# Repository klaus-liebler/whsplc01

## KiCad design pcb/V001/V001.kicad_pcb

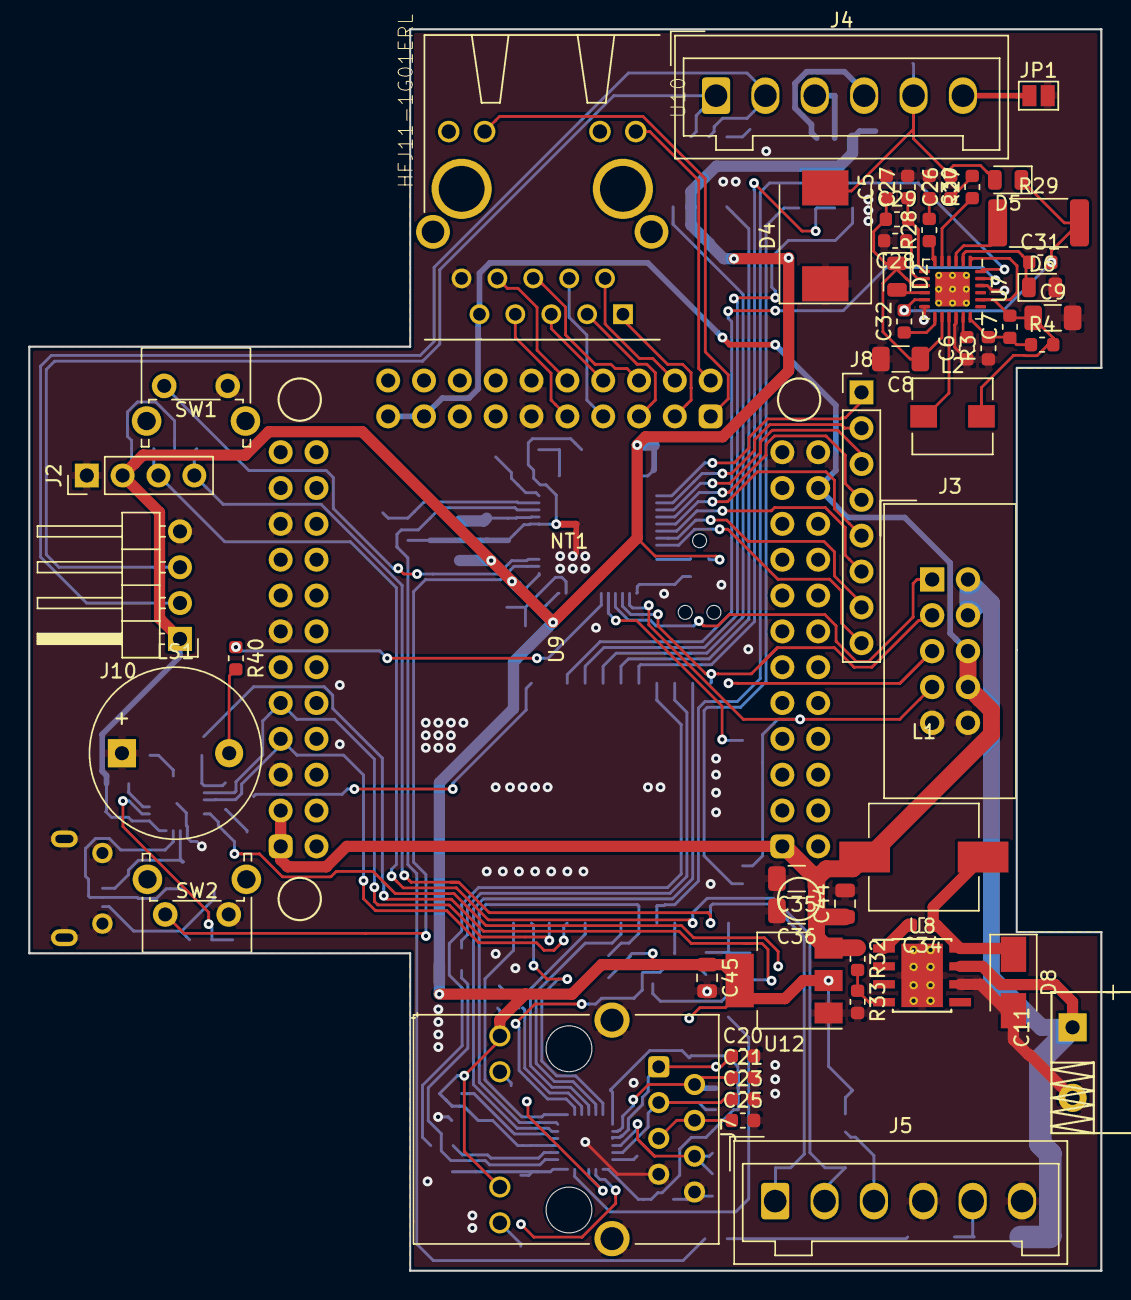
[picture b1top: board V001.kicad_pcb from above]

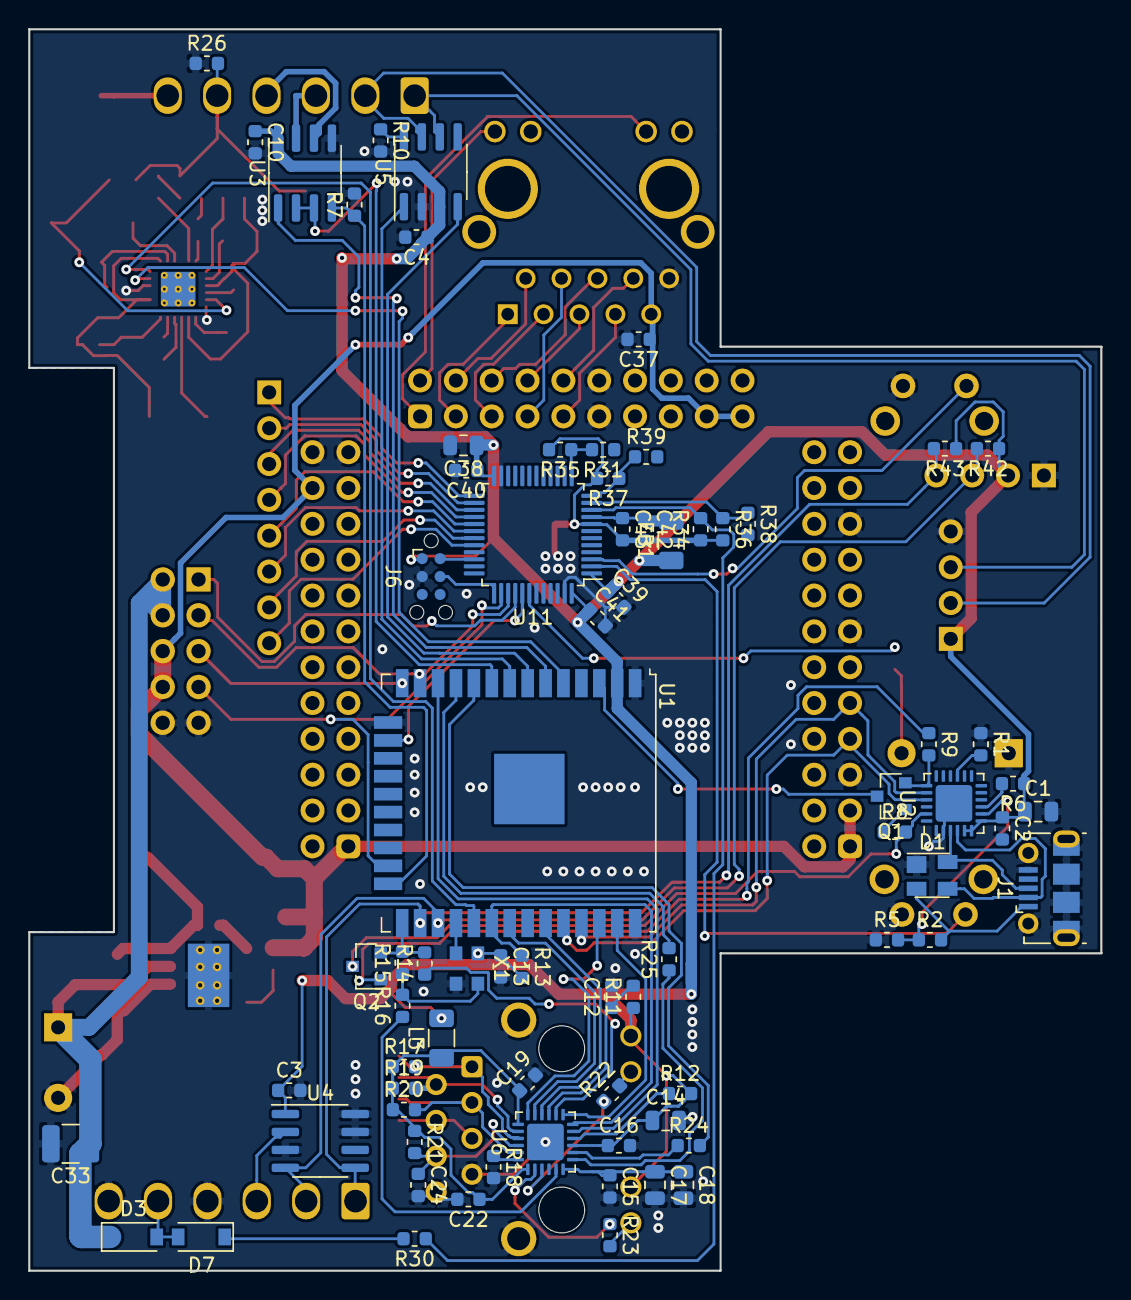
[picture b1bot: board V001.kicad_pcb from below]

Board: 2 copper layers, 76.0 x 88.0 mm, 128 parts (74 on the bottom side), 119 nets.

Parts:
C1: 4u7/6V3; C_0805_2012Metric
C2: u1/6V3; C_0603_1608Metric
C3, C4, C10, C12, C13, C16, C19, C22, C39, C40, C41: u1; C_0603_1608Metric
C5: CVDDHV; C_0603_1608Metric
C6: CSS; C_0603_1608Metric
C7: CFB1; C_0603_1608Metric
C8: CIN; C_1206_3216Metric
C9: COUT; C_1206_3216Metric
C11: 1000u/35V; CP_Radial_D10.0mm_P5.00mm_laydown
C14, C18, C38: 4u7; C_0805_2012Metric
C15: n47; C_0603_1608Metric
C17: 1u; C_0805_2012Metric
C20, C21, C23, C24: 12p; C_0603_1608Metric
C25: 22n; C_0603_1608Metric
C26: CPH; C_0603_1608Metric
C27: CFL; C_0603_1608Metric
C28: CREF; C_0603_1608Metric
C29: CFH; C_0603_1608Metric
C30: CPL; C_0603_1608Metric
C31: CAC; C_0603_1608Metric
C32: CGATE; C_0603_1608Metric
C33: 10u/35V; C_1210_3225Metric
C34, C43: 10n; C_0603_1608Metric
C35, C36: m1/6V3; C_1206_3216Metric
C37: u22; C_0603_1608Metric
C42: 1u; C_0603_1608Metric
C44, C45: 10u; C_0805_2012Metric
D1: SP0503BAHT; SOT-143
D2, D5, D6: TS4148RY; D_0805_2012Metric
D3, D7: D; D_SOD-123
D4: D_TVS; D_SMC
D8: SCKY; D_SMA
FB1: Ferrite_Bead_Small; L_1206_3216Metric
J1: USB_B_Micro; USB_Micro-B_Molex-105017-0001
J2: Display; PinHeader_1x04_P2.54mm_Vertical
J3: WHBUS; IDC-Header_2x05_P2.54mm_Vertical
J4: CU; Wago_734-136_1x06_P3.50mm_Vertical
J5: CD; Wago_734-136_1x06_P3.50mm_Vertical
J6: Conn_01x04; Tag-Connect_TC2030-IDC-NL_2x03_P1.27mm_Vertical
J7: 8P8C_LED_Shielded; RJ45_Hanrun_HR911105A
J8: Conn_01x08; PinHeader_1x08_P2.54mm_Vertical
J10: CAN; PinHeader_1x04_P2.54mm_Horizontal
JP1: Jumper; SolderJumper-2_P1.3mm_Open_Pad1.0x1.5mm
L1: 47u; L_Wuerth_WE-PD-Typ-M-Typ-S_Handsoldering
L2: L; L_Wuerth_HCI-5040
L3: FB; L_1206_3216Metric
LS1: Speaker_Crystal; Buzzer_12x9.5RM7.6
NT1: Net-Tie_2; NetTie-2_SMD_Pad0.5mm
Q1, Q2: Q_NPN_BEC; SOT-23
R1, R8, R9, R30, R31, R32, R33, R34, R35, R36, R37, R38, R39, R40: R; R_0603_1608Metric
R2: 22k1; R_0603_1608Metric
R3: RFB2; R_0603_1608Metric
R4: RFB1; R_0603_1608Metric
R5: 47k5; R_0603_1608Metric
R6, R42, R43: 2k2; R_0603_1608Metric
R7: 1k; R_0603_1608Metric
R10: 10k; R_0603_1608Metric
R11: 4k7; R_0603_1608Metric
R12: 10R; R_0603_1608Metric
R13: 1k5; R_0603_1608Metric
R14, R15, R16, R24, R25: 33R; R_0603_1608Metric
R17, R19, R20, R21: 49R9; R_0603_1608Metric
R18: 12k1; R_0603_1608Metric
R22, R23: k33; R_0603_1608Metric
R26: RDIS; R_0603_1608Metric
R27: RSH; R_0603_1608Metric
R28: RSL; R_0603_1608Metric
R29: RTX; R_2512_6332Metric
SW1, SW2: SW_Push; SW_Tactile_SPST_Angled_PTS645Vx83-2LFS
U1: ESP32-WROOM-32U
U2: CP2102N-A01-GQFN24; QFN-24-1EP_4x4mm_P0.5mm_EP2.6x2.6mm
U3: MAX485E; SOIC-8_3.9x4.9mm_P1.27mm
U4: DS2482; SOIC-8_3.9x4.9mm_P1.27mm
U5: SN65HVD230; SOIC-8_3.9x4.9mm_P1.27mm
U6: LAN8720A; QFN-24-1EP_4x4mm_P0.5mm_EP2.6x2.6mm
U7: STKNX; VQFN-24-1EP_4x4mm_P0.5mm_EP2.45x2.45mm_ThermalVias
U8: TPS5430DDA; TI_SO-PowerPAD-8_ThermalVias
U9: NanoPiCore; NanoPi NEO Core2
U10: HFJ11-1G01ERL; HALO_HFJ11-1G01ERL
U11: STM32F030C6Tx; LQFP-48_7x7mm_P0.5mm
U12: LM1117-3.3; SOT-223-3_TabPin2
X1: XO32; Oscillator_SMD_EuroQuartz_XO32-4Pin_3.2x2.5mm

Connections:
485_RTS: U1.9, U3.2, U3.3
485_RX: U1.6, U3.1
485_TX: R7.1, U1.24, U3.4
+3.3VA: C19.1, C22.1, L3.1, R17.1, R19.1, R20.1, R21.1, U6.1, U6.19
+3.3VADC: C42.1, C43.1, FB1.2, U11.9
+3V3: C1.1, C2.1, C3.1, C4.1, C10.1, C13.1, C14.1, C16.1, C38.1, C39.1, C40.1, C41.1, C45.1, FB1.1, J2.2, J6.1, J7.9, J7.11, J10.1, L3.2, R6.1, R11.1, R12.2, R13.2, R42.1, R43.1, U1.2, U2.5, U2.6, U2.7, U3.8, U4.1, U5.3, U6.9, U11.1, U11.24, U11.48, U12.2, X1.4
+5V: C35.1, C36.1, C37.1, C44.1, J3.6, J3.8, L1.1, R32.1, U9.1, U9.22, U9.25, U9.27, U9.65, U9.67, U10.9, U12.3
+24V: C11.1, C33.1, D3.1, J3.2, J3.4, U8.7
/1Wire: J5.3, U4.2
/CANH: J4.2, J10.2, U5.7
/CANL: J4.1, J10.3, U5.6
/EN: Q1.3, U1.3
/PWRIN: D3.2, D7.2, J5.5
/RS485A: J4.3, U3.7
/RS485B: J4.4, U3.6
/eth/CLKIN: R16.1, U6.5
/eth/CLKOUT: R15.1, R16.2, X1.3
/eth/INT: R14.1, U6.14
/eth/LED1: R22.1, U6.3
/eth/LED2: R23.1, U6.2
/eth/RBIAS: R18.1, U6.24
/eth/RNX: C24.1, J7.6, R21.2, U6.22
/eth/RST: C12.1, R11.2, U6.15
/eth/RXD0: R24.1, U6.8
/eth/RXD1: R25.1, U6.7
/eth/RXER: R12.1, U6.10
/eth/RXP: C23.1, J7.3, R20.2, U6.23
/eth/TXN: C21.1, J7.2, R19.2, U6.20
/eth/TXP: C20.1, J7.1, R17.2, U6.21
/ioext/IO1: J8.1, U11.25
/ioext/IO2: J8.2, U11.26
/ioext/IO3: J8.3, U11.27
/ioext/IO4: J8.4, U11.28
/ioext/IO5: J8.5, U11.29
/ioext/IO6: J8.6, U11.30
/ioext/IO7: J8.7, U11.31
/ioext/IO8: J8.8, U11.32
/ioext/SWCLK: J6.4, U11.37
/ioext/SWDIO: J6.2, U11.34
/knx/DCDC_IN: C5.1, C8.1, C29.1, D2.1, U7.9, U7.14
ADC_PWR: D7.1, R30.2
BUT0: SW1.1, U11.3
BUT1: SW2.2, U11.2
CAN_RX: U1.7, U5.4
CAN_TX: U1.8, U5.1
DBG_RX: U1.34, U2.21, U9.31
DBG_TX: U1.35, U2.20, U9.33
EMAC_RXD0: R24.2, U1.10
EMAC_RXD1: R25.2, U1.11
EMAC_RX_DV: U1.12, U6.11
EMAC_TXD0: U1.31, U6.17
EMAC_TXD1: U1.36, U6.18
EMAC_TX_CLK: Q2.2, R14.2, R15.2, U1.25
EMAC_TX_EN: U1.33, U6.16
GND: C1.2, C2.2, C3.2, C4.2, C5.2, C6.1, C8.2, C9.2, C10.2, C11.2, C12.2, C13.2, C14.2, C15.2, C16.2, C17.2, C18.2, C19.2, C20.2, C21.2, C22.2, C23.2, C24.2, C25.2, C27.2, C28.2, C30.1, C33.2, C35.2, C36.2, C37.2, C38.2, C39.2, C40.2, C41.2, C44.2, C45.2, D1.1, D4.1, D6.2, D8.2, J1.5, J1.6, J2.1, J3.9, J3.10, J5.4, J5.6, J6.3, J7.7, J7.8, J7.SH, J10.4, JP1.2, LS1.1, NT1.1, R1.1, R3.1, R5.1, R7.2, R10.2, R18.2, R26.1, R33.2, SW1.2, SW2.1, U1.1, U1.15, U1.38, U2.2, U2.25, U3.5, U4.3, U4.7, U4.8, U5.2, U6.25, U7.4, U7.12, U7.16, U7.22, U8.6, U8.9, U9.23, U9.24, U9.29, U9.37, U9.43, U9.59, U9.60, U10.10, U11.23, U11.47, U12.1, X1.2
GNDA: C42.2, C43.2, NT1.2, R34.1, R35.2, R36.2, R37.2, U11.8
I2C_SCL: J2.3, J5.2, R42.2, U1.27, U4.4
I2C_SDA: J2.4, J5.1, R43.2, U1.26, U4.5
KNX+: C26.2, D4.2, D5.2, J4.5, R26.2
KNX-: J4.6, JP1.1
KNXVOUT: C7.2, C9.1, L2.2, R4.2, U7.1, U7.20
KNX_RX: U1.5, U7.23
KNX_TX: U1.29, U7.24
NET_D1+: U9.51, U10.1
NET_D1-: U9.52, U10.2
NET_D2+: U9.53, U10.3
NET_D2-: U9.54, U10.6
NET_D3+: U9.55, U10.4
NET_D3-: U9.56, U10.5
NET_D4+: U9.57, U10.7
NET_D4-: U9.58, U10.8
NET_LNK: U9.49, U10.13
NET_SPD: U9.50, U10.11
unnamed: C6.2, U7.17
unnamed: C7.1, R3.2, R4.1, U7.18
unnamed: C15.1, C17.1, C18.1, U6.6
unnamed: C25.1, J7.4, J7.5
unnamed: C26.1, R27.2
unnamed: C27.1, C29.2, U7.7
unnamed: C28.1, U7.8
unnamed: C30.2, R28.2
unnamed: C31.1, D6.1, U7.2
unnamed: C31.2, C32.2, D5.1, R29.2, U7.11
unnamed: C32.1, U7.13
unnamed: C34.1, D8.1, L1.2, U8.8
unnamed: C34.2, U8.1
unnamed: D1.2, J1.1, R2.2
unnamed: D1.3, J1.2, U2.4
unnamed: D1.4, J1.3, U2.3
unnamed: D2.2, U7.10
unnamed: J7.10, R22.2
unnamed: J7.12, R23.2
unnamed: L2.1, U7.15
unnamed: LS1.2, R40.2
unnamed: Q1.1, R8.1
unnamed: Q1.2, R9.2, U2.19
unnamed: Q2.1, R9.1
unnamed: Q2.3, R8.2, U2.23
unnamed: R1.2, U2.15
unnamed: R2.1, R5.2, U2.8
unnamed: R6.2, U2.9
unnamed: R10.1, U5.8
unnamed: R27.1, U7.5
unnamed: R28.1, U7.6
unnamed: R29.1, U7.3
unnamed: R30.1, R34.2, U11.10
unnamed: R31.2, R35.1, U11.13
unnamed: R32.2, R33.1, U8.4
unnamed: R36.1, R38.1, U11.11
unnamed: R37.1, R39.1, U11.12
unnamed: R40.1, U11.42
PHY_POWER: U1.28, X1.1
SMI_MDC: U1.37, U6.13
SMI_MDIO: R13.1, U1.30, U6.12
SPI_CLK: J3.3, U1.13, U11.39
SPI_MISO: J3.5, U1.14
SPI_MOSI: J3.1, U11.40
SPI_MOSIX: U1.16, U11.41
SPI_STROBE: J3.7, U1.23, U11.38

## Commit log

2020-04-13 merged repository
2020-04-13 Bump js-yaml from 3.12.1 to 3.13.1 in /plcwebide
    Bumps [js-yaml](https://github.com/nodeca/js-yaml) from 3.12.1 to 3.13.1.
    - [Release notes](https://github.com/nodeca/js-yaml/releases)
    - [Changelog](https://github.com/nodeca/js-yaml/blob/master/CHANGELOG.md)
    - [Commits](https://github.com/nodeca/js-yaml/compare/3.12.1...3.13.1)
2020-07-20 Bump lodash from 4.17.15 to 4.17.19 in /plcwebide
    Bumps [lodash](https://github.com/lodash/lodash) from 4.17.15 to 4.17.19.
    - [Release notes](https://github.com/lodash/lodash/releases)
    - [Commits](https://github.com/lodash/lodash/compare/4.17.15...4.17.19)
2020-08-01 Bump elliptic from 6.5.2 to 6.5.3 in /plcwebide
    Bumps [elliptic](https://github.com/indutny/elliptic) from 6.5.2 to 6.5.3.
    - [Release notes](https://github.com/indutny/elliptic/releases)
    - [Commits](https://github.com/indutny/elliptic/compare/v6.5.2...v6.5.3)
2020-12-12 Bump ini from 1.3.5 to 1.3.8 in /plcwebide
    Bumps [ini](https://github.com/isaacs/ini) from 1.3.5 to 1.3.8.
    - [Release notes](https://github.com/isaacs/ini/releases)
    - [Commits](https://github.com/isaacs/ini/compare/v1.3.5...v1.3.8)
2021-03-10 Bump elliptic from 6.5.2 to 6.5.4 in /plcwebide
    Bumps [elliptic](https://github.com/indutny/elliptic) from 6.5.2 to 6.5.4.
    - [Release notes](https://github.com/indutny/elliptic/releases)
    - [Commits](https://github.com/indutny/elliptic/compare/v6.5.2...v6.5.4)
2021-03-31 Bump y18n from 3.2.1 to 3.2.2 in /plcwebide
    Bumps [y18n](https://github.com/yargs/y18n) from 3.2.1 to 3.2.2.
    - [Release notes](https://github.com/yargs/y18n/releases)
    - [Changelog](https://github.com/yargs/y18n/blob/master/CHANGELOG.md)
    - [Commits](https://github.com/yargs/y18n/commits)
2021-04-30 Bump ssri from 6.0.1 to 6.0.2 in /plcwebide
    Bumps [ssri](https://github.com/npm/ssri) from 6.0.1 to 6.0.2.
    - [Release notes](https://github.com/npm/ssri/releases)
    - [Changelog](https://github.com/npm/ssri/blob/v6.0.2/CHANGELOG.md)
    - [Commits](https://github.com/npm/ssri/compare/v6.0.1...v6.0.2)
2021-05-11 Bump lodash from 4.17.15 to 4.17.21 in /plcwebide
    Bumps [lodash](https://github.com/lodash/lodash) from 4.17.15 to 4.17.21.
    - [Release notes](https://github.com/lodash/lodash/releases)
    - [Commits](https://github.com/lodash/lodash/compare/4.17.15...4.17.21)
2021-05-11 Bump hosted-git-info from 2.8.8 to 2.8.9 in /plcwebide
    Bumps [hosted-git-info](https://github.com/npm/hosted-git-info) from 2.8.8 to 2.8.9.
    - [Release notes](https://github.com/npm/hosted-git-info/releases)
    - [Changelog](https://github.com/npm/hosted-git-info/blob/v2.8.9/CHANGELOG.md)
    - [Commits](https://github.com/npm/hosted-git-info/compare/v2.8.8...v2.8.9)
2021-05-26 Bump browserslist from 4.11.1 to 4.16.6 in /plcwebide
    Bumps [browserslist](https://github.com/browserslist/browserslist) from 4.11.1 to 4.16.6.
    - [Release notes](https://github.com/browserslist/browserslist/releases)
    - [Changelog](https://github.com/browserslist/browserslist/blob/main/CHANGELOG.md)
    - [Commits](https://github.com/browserslist/browserslist/compare/4.11.1...4.16.6)
2021-06-17 Bump postcss from 7.0.8 to 7.0.36 in /plcwebide
    Bumps [postcss](https://github.com/postcss/postcss) from 7.0.8 to 7.0.36.
    - [Release notes](https://github.com/postcss/postcss/releases)
    - [Changelog](https://github.com/postcss/postcss/blob/main/CHANGELOG.md)
    - [Commits](https://github.com/postcss/postcss/compare/7.0.8...7.0.36)
    ---
    updated-dependencies:
2021-08-12 Bump path-parse from 1.0.6 to 1.0.7 in /plcwebide
    Bumps [path-parse](https://github.com/jbgutierrez/path-parse) from 1.0.6 to 1.0.7.
    - [Release notes](https://github.com/jbgutierrez/path-parse/releases)
    - [Commits](https://github.com/jbgutierrez/path-parse/commits/v1.0.7)
    ---
    updated-dependencies:
    - dependency-name: path-parse
2022-02-10 Bump node-sass from 4.13.1 to 7.0.0 in /plcwebide
    Bumps [node-sass](https://github.com/sass/node-sass) from 4.13.1 to 7.0.0.
    - [Release notes](https://github.com/sass/node-sass/releases)
    - [Changelog](https://github.com/sass/node-sass/blob/master/CHANGELOG.md)
    - [Commits](https://github.com/sass/node-sass/compare/v4.13.1...v7.0.0)
    ---
    updated-dependencies:
2022-03-26 Bump minimist from 1.2.5 to 1.2.6 in /plcwebide
    Bumps [minimist](https://github.com/substack/minimist) from 1.2.5 to 1.2.6.
    - [Release notes](https://github.com/substack/minimist/releases)
    - [Commits](https://github.com/substack/minimist/compare/1.2.5...1.2.6)
    ---
    updated-dependencies:
    - dependency-name: minimist
2022-04-29 Bump async from 2.6.1 to 2.6.4 in /plcwebide
    Bumps [async](https://github.com/caolan/async) from 2.6.1 to 2.6.4.
    - [Release notes](https://github.com/caolan/async/releases)
    - [Changelog](https://github.com/caolan/async/blob/v2.6.4/CHANGELOG.md)
    - [Commits](https://github.com/caolan/async/compare/v2.6.1...v2.6.4)
    ---
    updated-dependencies:
2022-07-21 Bump terser from 4.6.10 to 4.8.1 in /plcwebide
    Bumps [terser](https://github.com/terser/terser) from 4.6.10 to 4.8.1.
    - [Release notes](https://github.com/terser/terser/releases)
    - [Changelog](https://github.com/terser/terser/blob/master/CHANGELOG.md)
    - [Commits](https://github.com/terser/terser/commits)
    ---
    updated-dependencies:
2022-10-06 Bump css-what from 2.1.2 to 2.1.3 in /plcwebide
    Bumps [css-what](https://github.com/fb55/css-what) from 2.1.2 to 2.1.3.
    - [Release notes](https://github.com/fb55/css-what/releases)
    - [Commits](https://github.com/fb55/css-what/compare/v2.1.2...v2.1.3)
    ---
    updated-dependencies:
    - dependency-name: css-what
2022-11-19 Bump loader-utils, html-webpack-plugin and webpack-cli in /plcwebide
    Bumps [loader-utils](https://github.com/webpack/loader-utils) to 1.4.2 and updates ancestor dependencies [loader-utils](https://github.com/webpack/loader-utils), [html-webpack-plugin](https://github.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
    Updates `loader-utils` from 1.2.3 to 1.4.2
    - [Release notes](https://github.com/webpack/loader-utils/releases)
    - [Changelog](https://github.com/webpack/loader-utils/blob/v1.4.2/CHANGELOG.md)
    - [Commits](https://github.com/webpack/loader-utils/compare/v1.2.3...v1.4.2)
    Updates `html-webpac
2022-12-05 Bump decode-uri-component from 0.2.0 to 0.2.2 in /plcwebide
    Bumps [decode-uri-component](https://github.com/SamVerschueren/decode-uri-component) from 0.2.0 to 0.2.2.
    - [Release notes](https://github.com/SamVerschueren/decode-uri-component/releases)
    - [Commits](https://github.com/SamVerschueren/decode-uri-component/compare/v0.2.0...v0.2.2)
    ---
    updated-dependencies:
    - dependency-name: decode-uri-component
2022-12-07 Bump qs from 6.5.2 to 6.5.3 in /plcwebide
    Bumps [qs](https://github.com/ljharb/qs) from 6.5.2 to 6.5.3.
    - [Release notes](https://github.com/ljharb/qs/releases)
    - [Changelog](https://github.com/ljharb/qs/blob/main/CHANGELOG.md)
    - [Commits](https://github.com/ljharb/qs/compare/v6.5.2...v6.5.3)
    ---
    updated-dependencies:
2022-12-07 Bump qs and express in /testwebserver
    Bumps [qs](https://github.com/ljharb/qs) to 6.11.0 and updates ancestor dependency [express](https://github.com/expressjs/express). These dependencies need to be updated together.
    Updates `qs` from 6.7.0 to 6.11.0
    - [Release notes](https://github.com/ljharb/qs/releases)
    - [Changelog](https://github.com/ljharb/qs/blob/main/CHANGELOG.md)
    - [Commits](https://github.com/ljharb/qs/compare/v6.7.0...v6.11.0)
    Updates `express` from 4.17.1 to 4.18.2
2022-12-12 Bump express from 4.17.1 to 4.17.3 in /plcwebide
    Bumps [express](https://github.com/expressjs/express) from 4.17.1 to 4.17.3.
    - [Release notes](https://github.com/expressjs/express/releases)
    - [Changelog](https://github.com/expressjs/express/blob/master/History.md)
    - [Commits](https://github.com/expressjs/express/compare/4.17.1...4.17.3)
    ---
    updated-dependencies:
2022-12-12 Bump express from 4.17.1 to 4.17.3 in /testwebserver
    Bumps [express](https://github.com/expressjs/express) from 4.17.1 to 4.17.3.
    - [Release notes](https://github.com/expressjs/express/releases)
    - [Changelog](https://github.com/expressjs/express/blob/master/History.md)
    - [Commits](https://github.com/expressjs/express/compare/4.17.1...4.17.3)
    ---
    updated-dependencies:
2023-01-07 Bump json5 and html-webpack-plugin in /plcwebide
    Bumps [json5](https://github.com/json5/json5) to 1.0.2 and updates ancestor dependency [html-webpack-plugin](https://github.com/jantimon/html-webpack-plugin). These dependencies need to be updated to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
    Updates `json5` from 1.0.1 to 1.0.2
    - [Release notes](https://github.com/json5/json5/releases)
    - [Changelog](https://github.com/json5/json5/blob/main/CHANGELOG.md)
    - [Commits](https://github.com/json5/json5/compare/v1.0.1...v1.0.2)
    Updates `html-webpack-plugin` from 3.2.0 to 5.5.0
